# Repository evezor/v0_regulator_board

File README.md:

# Voltage Regulator Board
*please note this board has been deprecated.

An edge board with an adjustable voltage regulator circuit capable of supplying 2A of current​

source files can be found here: https://github.com/evezor/v0_regulator_board

Evezor® and all associated marks, logos, and designs are registered trademarks and protected by copyright. Unauthorized use or reproduction of these trademarks and copyrighted materials is strictly prohibited.

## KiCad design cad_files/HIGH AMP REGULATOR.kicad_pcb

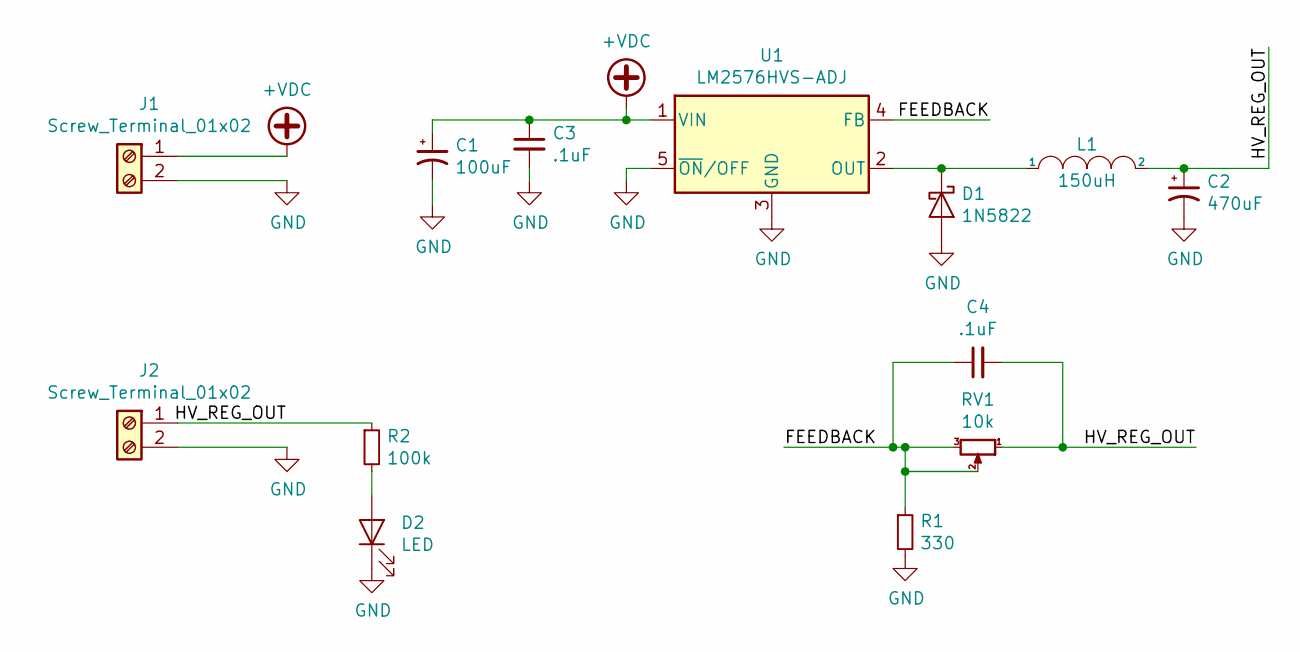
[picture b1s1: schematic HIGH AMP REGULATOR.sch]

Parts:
C1: 100uF; CP_Elec_10x10
C2: 470uF; CAPACITOR_12x
C3: .1uF; C_0805_2012Metric
C4: .1uF; C_0603_1608Metric
D1: 1N5822; D_SMC
D2: LED; LED_0603_1608Metric
J1, J2: Screw_Terminal_01x02; PhoenixContact_MC_1,5_2-G-3.81_1x02_P3.81mm_Horizontal
L1: 150uH; INDUCTOR_13.5x12.5x5.7
R1: 330; R_0603_1608Metric
R2: 100k; R_0603_1608Metric
RV1: 10k; Potentiometer_Bourns_3296W_Vertical
U1: LM2576HVS-ADJ; TO-263-5_TabPin3

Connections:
+VDC: C1.1, C3.1, J1.1, U1.1 (VIN)
/FEEDBACK: C4.1, R1.1, RV1.2, RV1.3, U1.4 (FB)
/HV_REG_OUT: C2.1, C4.2, J2.1, L1.2, R2.1, RV1.1
GND: C1.2, C2.2, C3.2, D1.2 (A), D2.1 (K), J1.2, J2.2, R1.2, U1.3 (GND), U1.5 (~ON~/OFF)
unnamed: D1.1 (K), L1.1, U1.2 (OUT)
unnamed: D2.2 (A), R2.2

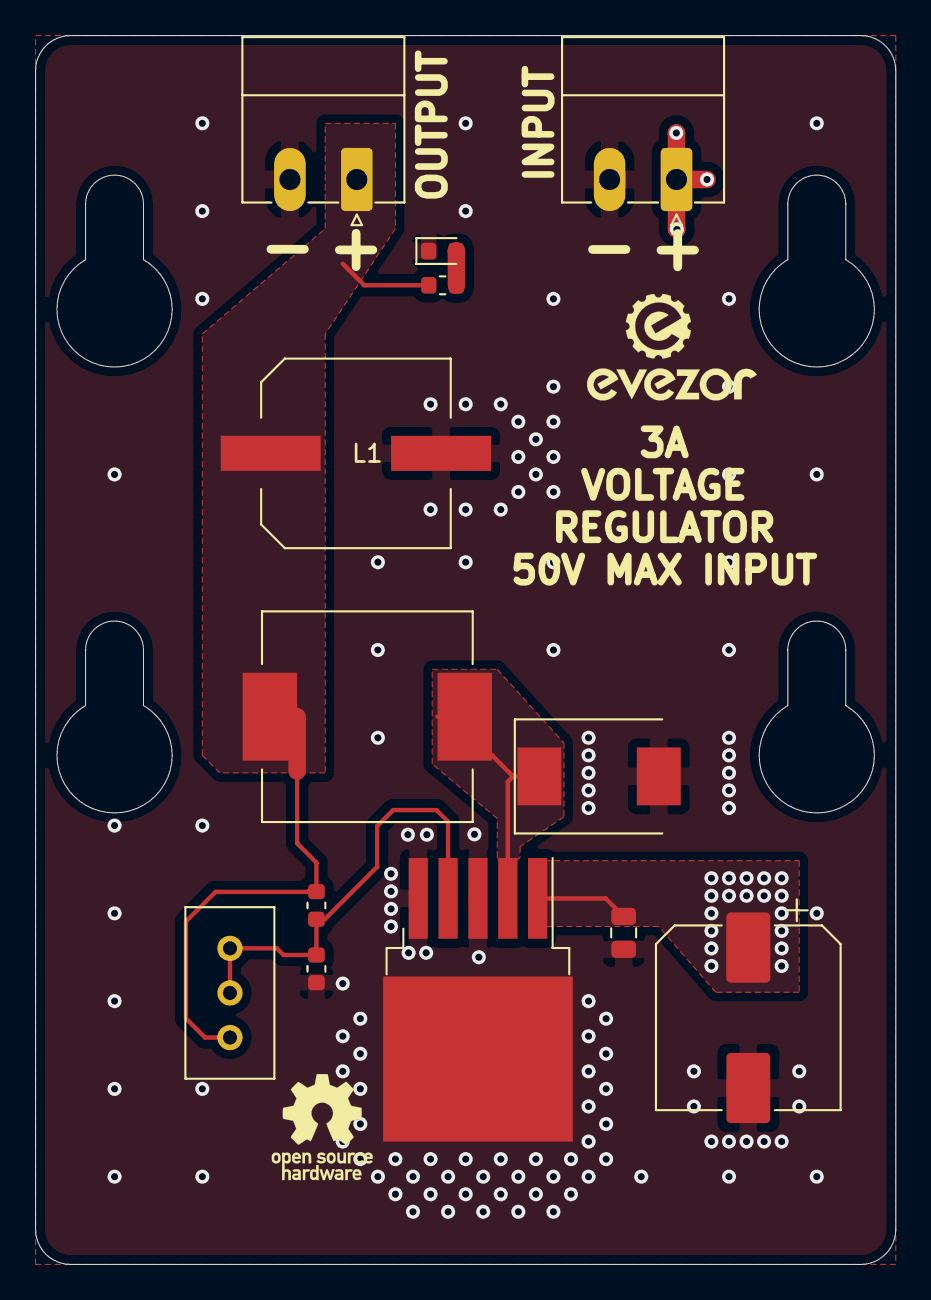
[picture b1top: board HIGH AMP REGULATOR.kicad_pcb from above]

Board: 2 copper layers, 49.0 x 70.0 mm, 13 parts (0 on the bottom side), 6 nets.

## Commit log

2023-09-11 init
